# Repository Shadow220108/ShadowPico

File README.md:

# SHADOW PICO  
It is a handheld device that works on Raspberry Pi Pico

# Model  
This is the final look of the device  

I have added a small hole on the side for usb  

On the front there are 3 holes for the SD Card , External Connector and a Slide switch for power  

I have used ridges to attach the bottom case to the top case!  
Bottom Case :  
  
Top Case :  

# PCB  
This is the PCB ( ground pour is hidden )  

And here are the schematics!  

# Firmware  
I have uploaded the basic code for arduino to identify buttons right now , will add the games after i get the card!  

# BOM  
|PRODUCT                 |QUANTITY  |PER UNIT COST|TOTAL COST |PRODUCT LINK                                                                                                                                                                                                                                                                                                                                                                                                                                                     |
|------------------------|----------|-------------|-----------|-----------------------------------------------------------------------------------------------------------------------------------------------------------------------------------------------------------------------------------------------------------------------------------------------------------------------------------------------------------------------------------------------------------------------------------------------------------------|
|                        |          |             |           |                                                                                                                                                                                                                                                                                                                                                                                                                                                                 |
|Raspberry Pi Pico       |1         |4$           |4$         |https://robu.in/product/raspberry-pi-pico/                                                                                                                                                                                                                                                                                                                                                                                                                       |
|                        |          |             |           |                                                                                                                                                                                                                                                                                                                                                                                                                                                                 |
|Waveshare 2 inch LD     |1         |10.40$       |14.40$     |https://robu.in/product/waveshare-2-inch-lcd-display-module-240x320/                                                                                                                                                                                                                                                                                                                                                                                             |
|                        |          |             |           |                                                                                                                                                                                                                                                                                                                                                                                                                                                                 |
|TP4056 ( Charging IC )  |1         |0.13$        |14.53$     |https://robu.in/product/1-month-warranty-1253/                                                                                                                                                                                                                                                                                                                                                                                                                   |
|                        |          |             |           |                                                                                                                                                                                                                                                                                                                                                                                                                                                                 |
|MMBT2222A ( Transistor )|1         |0.02$        |14.55$     |https://robu.in/product/mmbt2222a-tp-mcc-40v-350mw-100150ma10v-600ma-npn-sot-23-bipolar-bjt-rohs/                                                                                                                                                                                                                                                                                                                                                                |
|                        |          |             |           |                                                                                                                                                                                                                                                                                                                                                                                                                                                                 |
|Diodes                  |3         |0.03$        |14.64$     |https://robu.in/product/ss12-slkor-20v-500mv1a-1a-smado-214ac-schottky-diodes-rohs/                                                                                                                                                                                                                                                                                                                                                                              |
|                        |          |             |           |                                                                                                                                                                                                                                                                                                                                                                                                                                                                 |
|Resistors               |8         |0.03$        |14.88$     |https://robu.in/product/rt0805brd071kl-yageo-125mw-thin-film-resistor-150v-%c2%b125ppm-%e2%84%83-%c2%b10-1-1k%cf%89-0805-chip-resistor-surface-mount-rohs/                                                                                                                                                                                                                                                                                                       |
|                        |          |             |           |                                                                                                                                                                                                                                                                                                                                                                                                                                                                 |
|Capacitor               |3         |0.01$        |14.91$     |https://robu.in/product/100nf-0805-surface-mount-multilayer-ceramic-capacitor-pack-of-40/                                                                                                                                                                                                                                                                                                                                                                        |
|                        |          |             |           |                                                                                                                                                                                                                                                                                                                                                                                                                                                                 |
|PCB                     |5(minimum)|2$           |25.67$     |https://jlpcb.com                                                                                                                                                                                                                                                                                                                                                                                                                                                |
|                        |          |             |           |                                                                                                                                                                                                                                                                                                                                                                                                                                                                 |
|LED                     |4         |0.01$        |25.70$     |https://robu.in/product/0805-surface-mount-led-yellow/                                                                                                                                                                                                                                                                                                                                                                                                           |
|                        |          |             |           |                                                                                                                                                                                                                                                                                                                                                                                                                                                                 |
|Tactile Switches        |10        |0.01$        |25.87$     |https://robu.in/product/6x6x5-tactile-push-button-switch/                                                                                                                                                                                                                                                                                                                                                                                                        |
|                        |          |             |           |                                                                                                                                                                                                                                                                                                                                                                                                                                                                 |
|Slide Switch            |1         |0.07$        |26$        |https://robu.in/product/1-month-warranty-257/                                                                                                                                                                                                                                                                                                                                                                                                                    |
|                        |          |             |           |                                                                                                                                                                                                                                                                                                                                                                                                                                                                 |
|External Header         |1         |0.50$        |26.50$     |https://robu.in/product/ds1029-10-2x6p8bva1-b-connfly-2x6-pin-2-54mm-pin-header-double-row-stack-v-t-w-post-type/                                                                                                                                                                                                                                                                                                                                                |
|                        |          |             |           |                                                                                                                                                                                                                                                                                                                                                                                                                                                                 |
|Buzzer                  |1         |0.50$        |27$        |https://robu.in/product/1-month-warranty-1231/                                                                                                                                                                                                                                                                                                                                                                                                                   |
|                        |          |             |           |                                                                                                                                                                                                                                                                                                                                                                                                                                                                 |
|LiPo Cell 3.7V Battery  |1         |4$           |31$        |https://robu.in/product/950mah-pcm-protected-micro-li-po-battery/                                                                                                                                                                                                                                                                                                                                                                                                |
|                        |          |             |           |                                                                                                                                                                                                                                                                                                                                                                                                                                                                 |
|SD Card Reader          |1         |0.50$        |31.50$     |https://robu.in/product/sd-card-reading-writing-module-arduino/#tab-questions                                                                                                                                                                                                                                                                                                                                                                                    |
|                        |          |             |           |                                                                                                                                                                                                                                                                                                                                                                                                                                                                 |
|SD Card                 |1         |3$           |34$        |https://www.flipkart.com/avoc-flash-mc016-microsdxc-16-gb-microsd-card-class-10-20-mb-s-memory-compatible-tablet-mobile-camera/p/itm6992565b2daec?pid=ACCHG3F8GXFTJ2ZB&lid=LSTACCHG3F8GXFTJ2ZBBBBRM3&marketplace=FLIPKART&store=6bo%2Fjdy%2Ftby&spotlightTagId=default_TrendingId_6bo%2Fjdy%2Ftby&srno=b_1_4&otracker=browse&fm=organic&iid=b3d76566-40fa-4945-9e8a-c26acff24796.ACCHG3F8GXFTJ2ZB.SEARCH&ppt=browse&ppn=browse&ssid=o5mxucwjzzgcimtc1765750789965|
|                        |          |             |           |                                                                                                                                                                                                                                                                                                                                                                                                                                                                 |
|3D Print                |          |3-4$         |38$        |                                                                                                                                                                                                                                                                                                                                                                                                                                                                 |
|                        |          |             |           |                                                                                                                                                                                                                                                                                                                                                                                                                                                                 |
|                        |          |TOTAL        |40$ Approx!|                                                                                                                                                                                                                                                                                                                                                                                                                                                                 |

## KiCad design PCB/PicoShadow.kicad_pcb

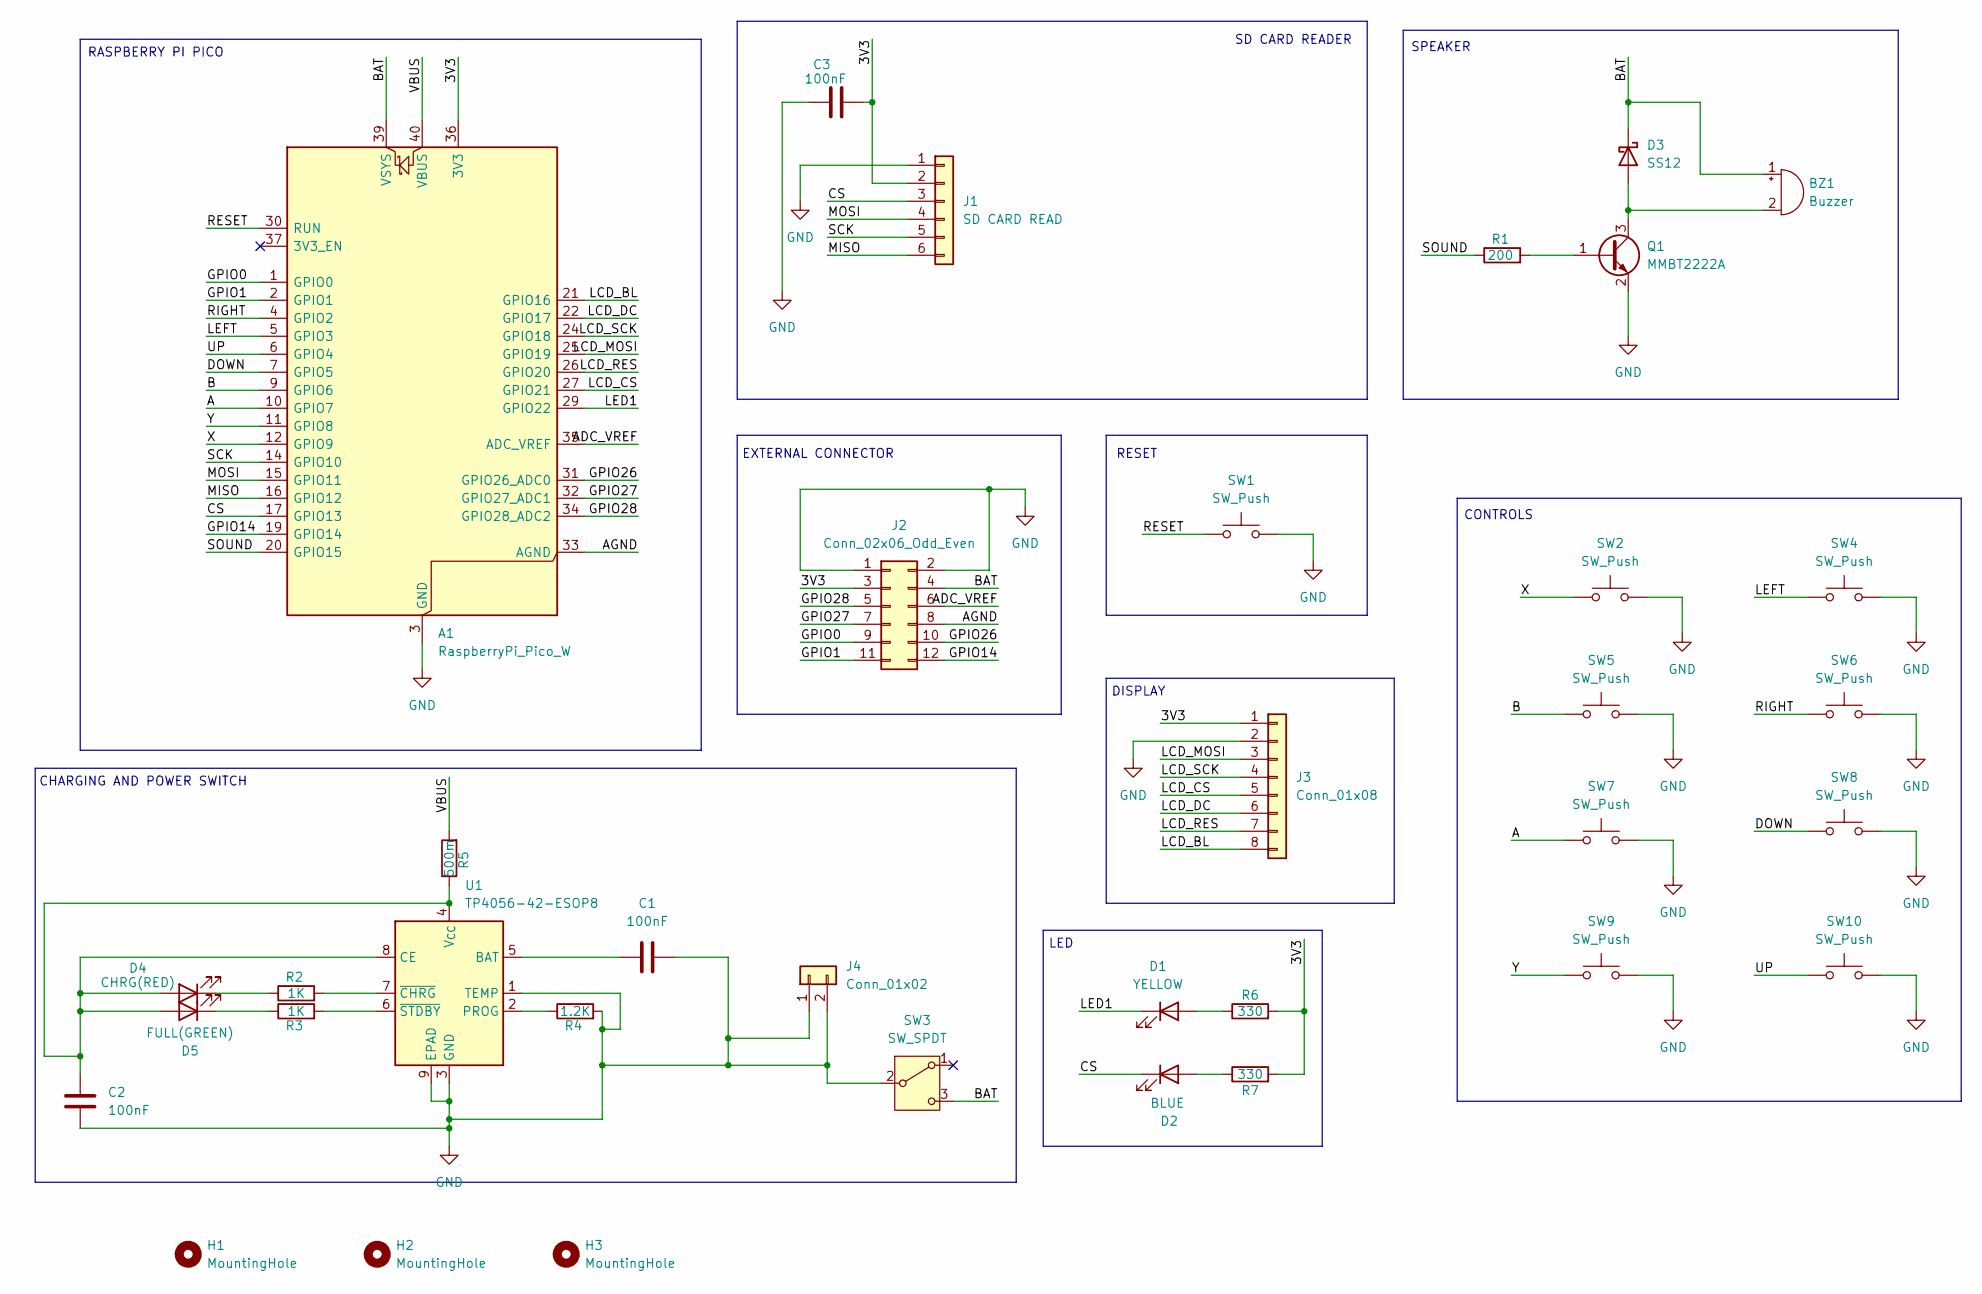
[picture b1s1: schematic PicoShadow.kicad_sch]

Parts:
A1: RaspberryPi_Pico_W; RaspberryPi_Pico_SMD
BZ1: Buzzer; Buzzer_12x9.5RM7.6
C1, C2, C3: 100nF; C_0805_2012Metric
D1: YELLOW; LED_0805_2012Metric
D2: BLUE; LED_0805_2012Metric
D3: SS12; D_SMA
D4: CHRG(RED); LED_0805_2012Metric
D5: FULL(GREEN); LED_0805_2012Metric
H1, H2, H3: MountingHole; MountingHole_2.2mm_M2
J1: SD CARD READ; PinHeader_1x06_P2.54mm_Vertical
J2: Conn_02x06_Odd_Even; PinHeader_2x06_P2.54mm_Vertical
J3: Conn_01x08; PinSocket_1x08_P2.54mm_Vertical
J4: Conn_01x02; PinHeader_1x02_P2.54mm_Vertical
Q1: MMBT2222A; SOT-23
R1: 200; R_0805_2012Metric
R2, R3: 1K; R_0805_2012Metric
R4: 1.2K; R_0805_2012Metric
R5: 500m; R_0805_2012Metric
R6, R7: 330; R_0805_2012Metric
SW1, SW2, SW4, SW5, SW6, SW7, SW8, SW9, SW10: SW_Push; SW_PUSH_6mm
SW3: SW_SPDT; SW_Slide_SP3T_Straight_CK_OS103012MU1QP1
U1: TP4056-42-ESOP8; SOIC-8-1EP_3.9x4.9mm_P1.27mm_EP2.29x3mm

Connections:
/3V3: A1.36 (3V3), C3.2, J1.2, J2.3, J3.1, R6.2, R7.2
/A: A1.10 (GPIO7), SW7.1
/ADC_VREF: A1.35 (ADC_VREF), J2.6
/AGND: A1.33 (AGND), J2.8
/B: A1.9 (GPIO6), SW5.1
/BAT: A1.39 (VSYS), BZ1.1 (+), D3.1 (K), J2.4, SW3.3 (C)
/CS: A1.17 (GPIO13), D2.1 (K), J1.3
/DOWN: A1.7 (GPIO5), SW8.1
/GPIO0: A1.1 (GPIO0), J2.9
/GPIO1: A1.2 (GPIO1), J2.11
/GPIO14: A1.19 (GPIO14), J2.12
/GPIO26: A1.31 (GPIO26_ADC0), J2.10
/GPIO27: A1.32 (GPIO27_ADC1), J2.7
/GPIO28: A1.34 (GPIO28_ADC2), J2.5
/LCD_BL: A1.21 (GPIO16), J3.8
/LCD_CS: A1.27 (GPIO21), J3.5
/LCD_DC: A1.22 (GPIO17), J3.6
/LCD_MOSI: A1.25 (GPIO19), J3.3
/LCD_RES: A1.26 (GPIO20), J3.7
/LCD_SCK: A1.24 (GPIO18), J3.4
/LED1: A1.29 (GPIO22), D1.1 (K)
/LEFT: A1.5 (GPIO3), SW4.1
/MISO: A1.16 (GPIO12), J1.6
/MOSI: A1.15 (GPIO11), J1.4
/RESET: A1.30 (RUN), SW1.1
/RIGHT: A1.4 (GPIO2), SW6.1
/SCK: A1.14 (GPIO10), J1.5
/SOUND: A1.20 (GPIO15), R1.1
/UP: A1.6 (GPIO4), SW10.1
/VBUS: A1.40 (VBUS), R5.2
/X: A1.12 (GPIO9), SW2.1
/Y: A1.11 (GPIO8), SW9.1
GND: A1.3 (GND), A1.8 (GND), A1.13 (GND), A1.18 (GND), A1.23 (GND), A1.28 (GND), A1.38 (GND), C1.2, C2.2, C3.1, J1.1, J2.1, J2.2, J3.2, J4.1, J4.2, Q1.2 (E), R4.2, SW1.2, SW2.2, SW3.2 (B), SW4.2, SW5.2, SW6.2, SW7.2, SW8.2, SW9.2, SW10.2, U1.1 (TEMP), U1.3 (GND), U1.9 (EPAD)
unnamed: BZ1.2 (-), D3.2 (A), Q1.3 (C)
unnamed: D1.2 (A), R6.1
unnamed: D2.2 (A), R7.1
unnamed: C2.1, D4.2 (A), D5.2 (A), R5.1, U1.4 (V_{CC}), U1.8 (CE)
unnamed: D4.1 (K), R2.1
unnamed: D5.1 (K), R3.1
unnamed: Q1.1 (B), R1.2
unnamed: C1.1, U1.5 (BAT)
unnamed: R4.1, U1.2 (PROG)
unnamed: R2.2, U1.7 (~CHRG)
unnamed: R3.2, U1.6 (~STDBY)

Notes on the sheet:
CONTROLS
RASPBERRY PI PICO
SPEAKER
RESET
SD CARD READER
DISPLAY
CHARGING AND POWER SWITCH
LED
EXTERNAL CONNECTOR

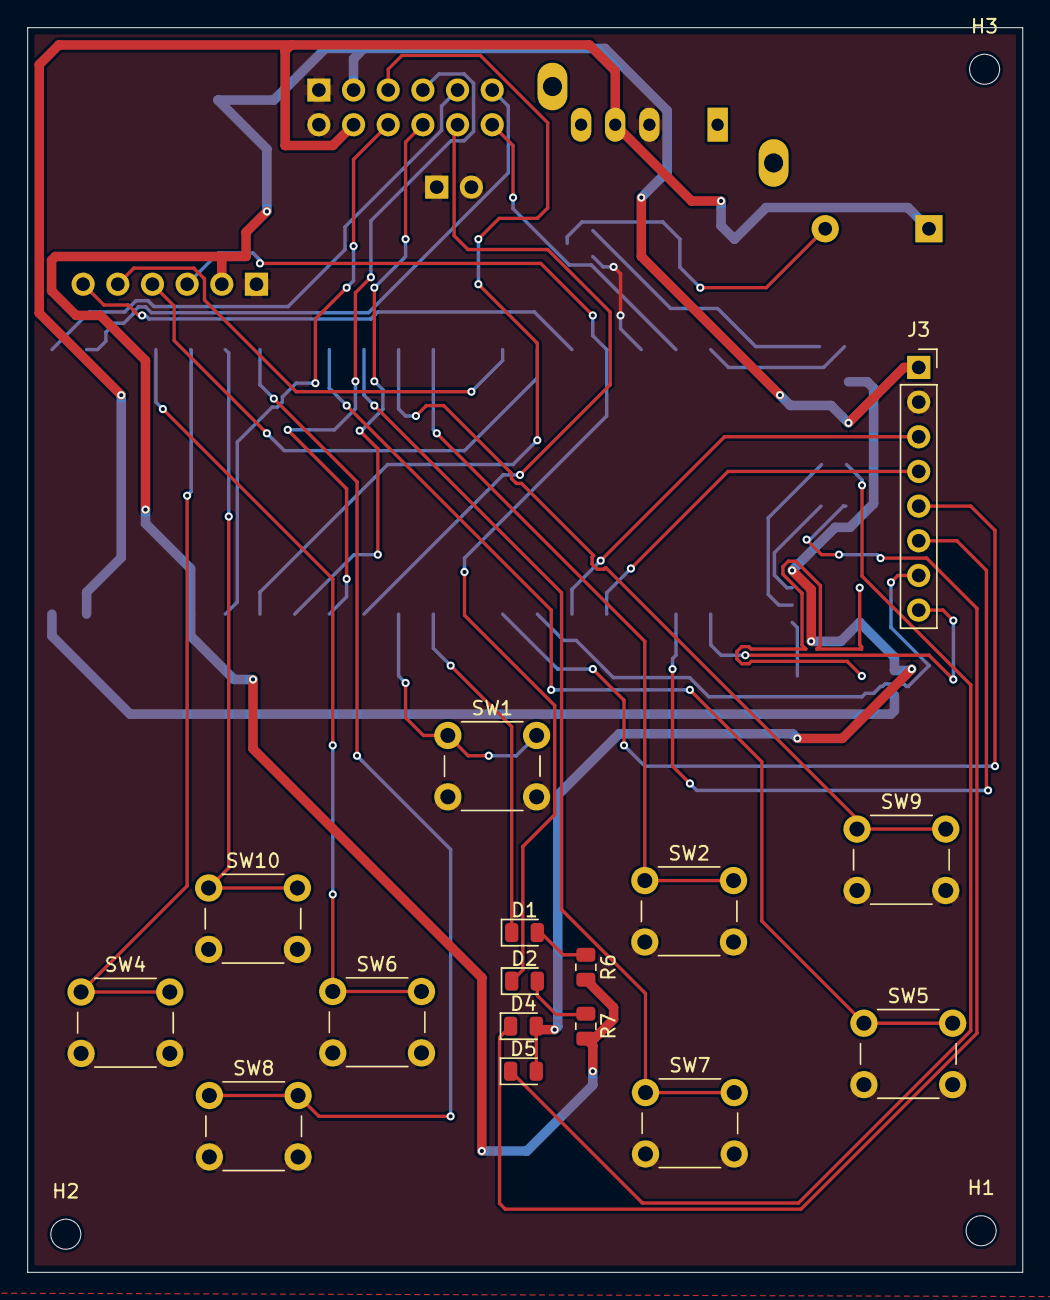
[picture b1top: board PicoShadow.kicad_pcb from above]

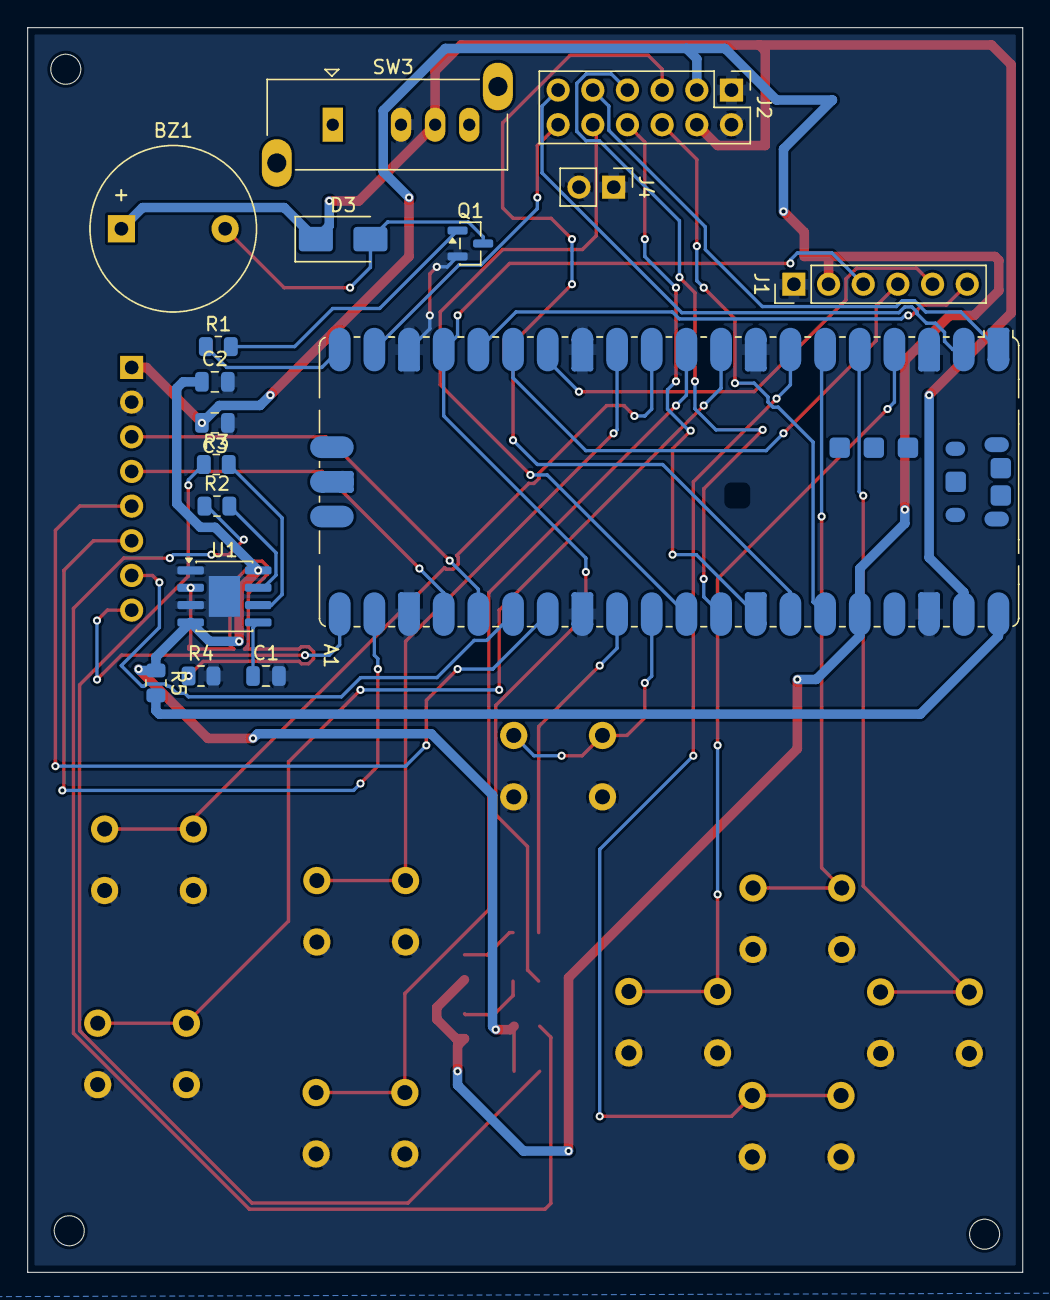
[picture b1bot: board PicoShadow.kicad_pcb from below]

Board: 2 copper layers, 72.9 x 91.2 mm, 36 parts (17 on the bottom side), 44 nets.

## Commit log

2025-12-14 Uploading Files from Local Repo!
